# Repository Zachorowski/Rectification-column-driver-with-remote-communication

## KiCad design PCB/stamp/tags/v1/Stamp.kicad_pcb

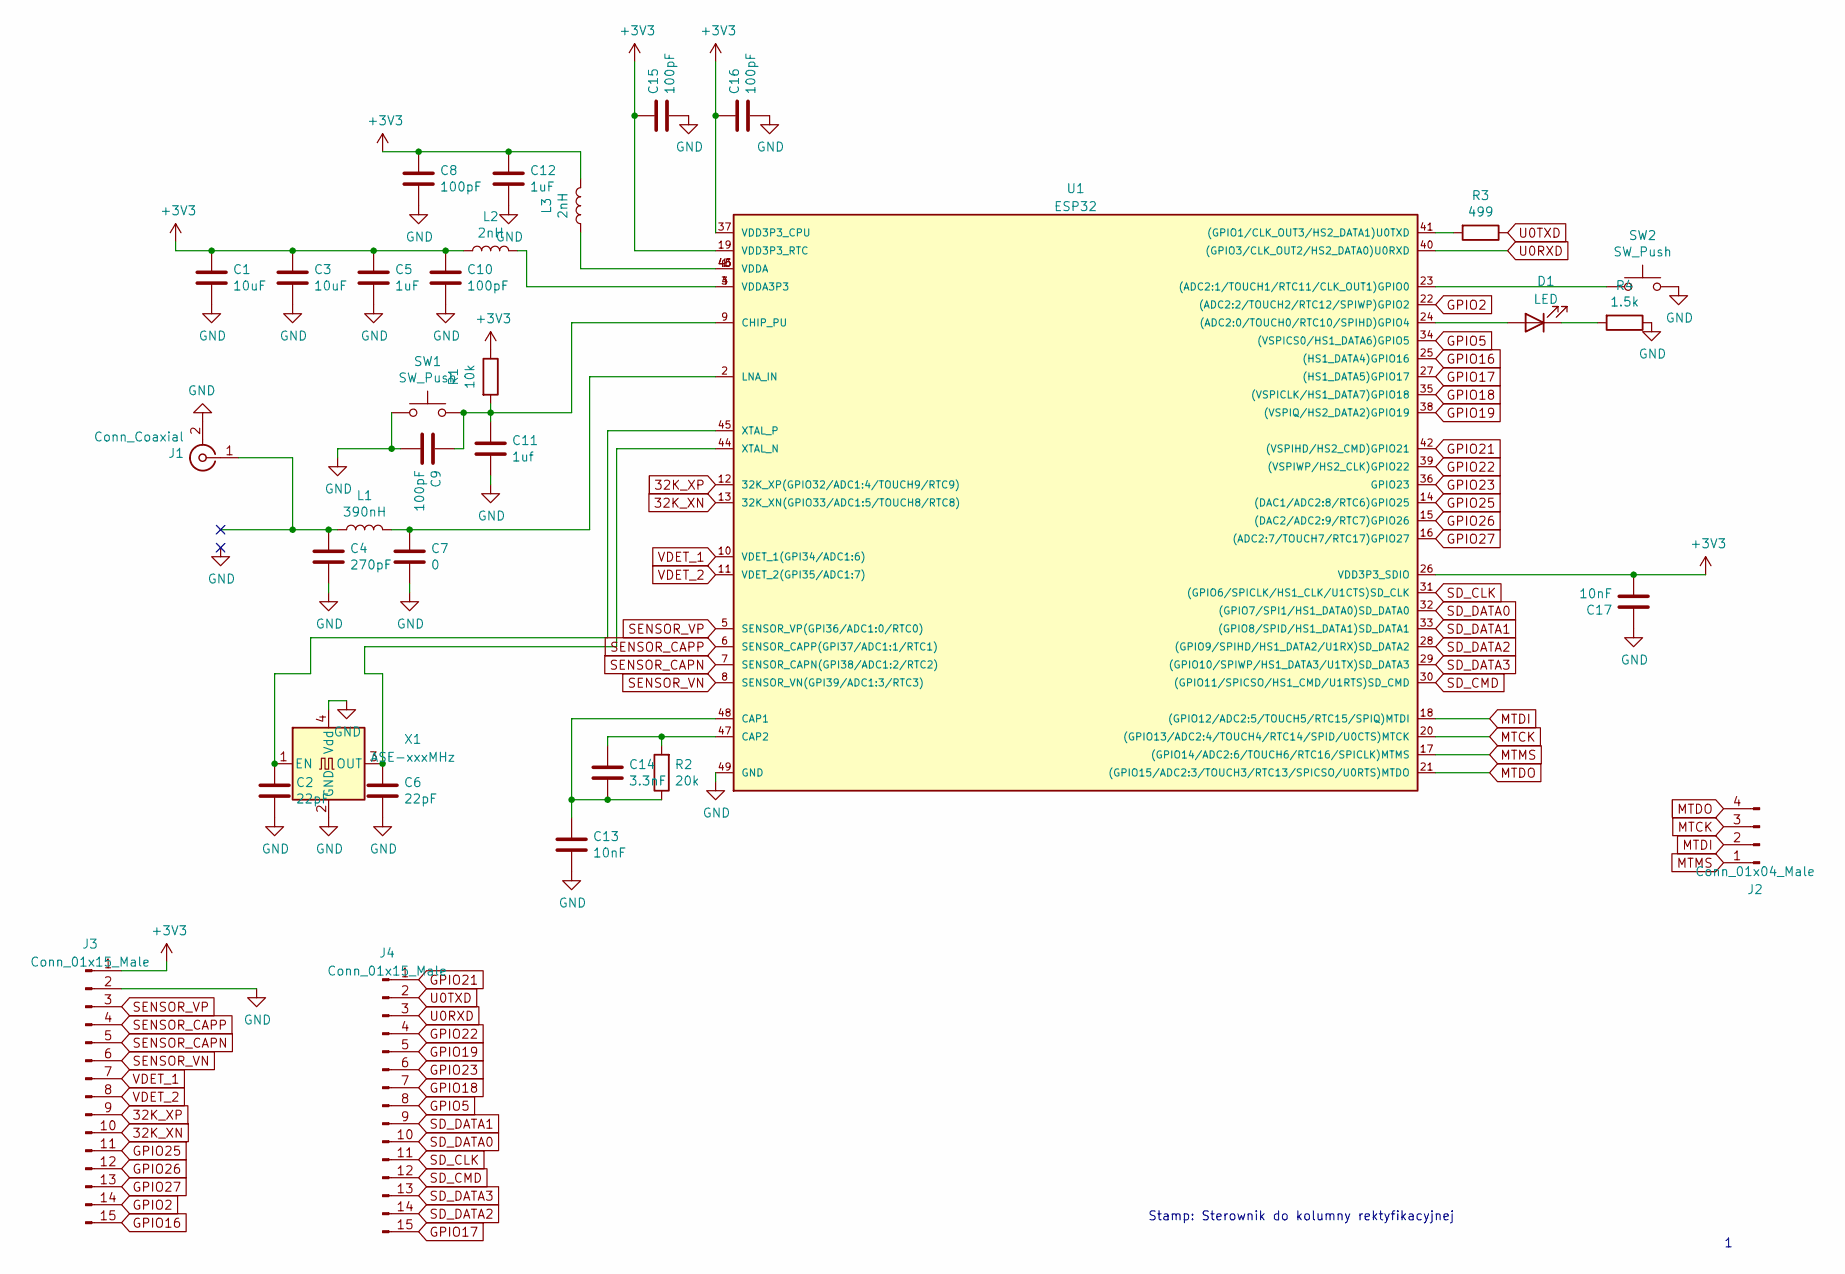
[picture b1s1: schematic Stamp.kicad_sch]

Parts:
C1, C3: 10uF; C_0603_1608Metric_Pad1.08x0.95mm_HandSolder
C2, C6: 22pF; C_0603_1608Metric_Pad1.08x0.95mm_HandSolder
C4: 270pF; C_0603_1608Metric_Pad1.08x0.95mm_HandSolder
C5, C12: 1uF; C_0603_1608Metric_Pad1.08x0.95mm_HandSolder
C7: 0; C_0603_1608Metric_Pad1.08x0.95mm_HandSolder
C8, C9, C10, C15, C16: 100pF; C_0603_1608Metric_Pad1.08x0.95mm_HandSolder
C11: 1uf; C_0603_1608Metric_Pad1.08x0.95mm_HandSolder
C13, C17: 10nF; C_0603_1608Metric_Pad1.08x0.95mm_HandSolder
C14: 3.3nF; C_0603_1608Metric_Pad1.08x0.95mm_HandSolder
D1: LED; LED_0805_2012Metric_Pad1.15x1.40mm_HandSolder
J1: Conn_Coaxial; U.FL_Molex_MCRF_73412-0110_Vertical
J2: Conn_01x04_Male; PinHeader_1x04_P2.54mm_Vertical
J3, J4: Conn_01x15_Male; PinHeader_1x15_P2.54mm_Vertical
L1: 390nH; L_0603_1608Metric_Pad1.05x0.95mm_HandSolder
L2, L3: 2nH; L_0603_1608Metric_Pad1.05x0.95mm_HandSolder
R1: 10k; R_0603_1608Metric_Pad0.98x0.95mm_HandSolder
R2: 20k; R_0603_1608Metric_Pad0.98x0.95mm_HandSolder
R3: 499; R_0603_1608Metric_Pad0.98x0.95mm_HandSolder
R4: 1.5k; R_0603_1608Metric_Pad0.98x0.95mm_HandSolder
SW1, SW2: SW_Push; SW_Push_1P1T_NO_6x6mm_H9.5mm
U1: ESP32; QFN-48-1EP_6x6mm_P0.4mm_EP4.3x4.3mm
X1: ASE-xxxMHz; Oscillator_SMD_SeikoEpson_SG210-4Pin_2.5x2.0mm_HandSoldering

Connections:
32K_XN: J3.10, U1.13 (32K_XN(GPIO33/ADC1:5/TOUCH8/RTC8))
32K_XP: J3.9, U1.12 (32K_XP(GPIO32/ADC1:4/TOUCH9/RTC9))
+3V3: C1.2, C3.2, C5.2, C8.2, C10.2, C12.2, C15.2, C16.2, C17.1, J3.1, L2.1, L3.2, R1.1, U1.19 (VDD3P3_RTC), U1.26 (VDD3P3_SDIO), U1.37 (VDD3P3_CPU)
GND: C1.1, C2.1, C3.1, C4.1, C5.1, C6.1, C7.1, C8.1, C9.1, C10.1, C11.1, C12.1, C13.1, C15.1, C16.1, C17.2, J1.2 (Ext), J3.2, R4.1, SW1.1, SW2.2, U1.49 (GND), X1.2 (GND), X1.4 (Vdd)
GPIO2: J3.14, U1.22 ((ADC2:2/TOUCH2/RTC12/SPIWP)GPIO2)
GPIO5: J4.8, U1.34 ((VSPICS0/HS1_DATA6)GPIO5)
GPIO16: J3.15, U1.25 ((HS1_DATA4)GPIO16)
GPIO17: J4.15, U1.27 ((HS1_DATA5)GPIO17)
GPIO18: J4.7, U1.35 ((VSPICLK/HS1_DATA7)GPIO18)
GPIO19: J4.5, U1.38 ((VSPIQ/HS2_DATA2)GPIO19)
GPIO21: J4.1, U1.42 ((VSPIHD/HS2_CMD)GPIO21)
GPIO22: J4.4, U1.39 ((VSPIWP/HS2_CLK)GPIO22)
GPIO23: J4.6, U1.36 (GPIO23)
GPIO25: J3.11, U1.14 ((DAC1/ADC2:8/RTC6)GPIO25)
GPIO26: J3.12, U1.15 ((DAC2/ADC2:9/RTC7)GPIO26)
GPIO27: J3.13, U1.16 ((ADC2:7/TOUCH7/RTC17)GPIO27)
MTCK: J2.3, U1.20 ((GPIO13/ADC2:4/TOUCH4/RTC14/SPID/U0CTS)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)
MTDI: J2.2, U1.18 ((GPIO12/ADC2:5/TOUCH5/RTC15/SPIQ)MTDI)
MTDO: J2.4, U1.21 ((GPIO15/ADC2:3/TOUCH3/RTC13/SPICSO/U0RT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)
MTMS: J2.1, U1.17 ((GPIO14/ADC2:6/TOUCH6/RTC16/SPICLK)MTMS)
unnamed: C2.2, U1.45 (XTAL_P), X1.1 (EN)
unnamed: C6.2, U1.44 (XTAL_N), X1.3 (OUT)
unnamed: C7.2, L1.2, U1.2 (LNA_IN)
unnamed: C9.2, C11.2, R1.2, SW1.2, U1.9 (CHIP_PU)
unnamed: C13.2, C14.1, R2.1, U1.48 (CAP1)
unnamed: C14.2, R2.2, U1.47 (CAP2)
unnamed: D1.1 (K), R4.2
unnamed: D1.2 (A), U1.24 ((ADC2:0/TOUCH0/RTC10/SPIHD)GPIO4)
unnamed: L2.2, U1.3 (VDDA3P3), U1.4 (VDDA3P3)
unnamed: L3.1, U1.1 (VDDA), U1.43 (VDDA), U1.46 (VDDA)
unnamed: R3.2, U1.41 ((GPIO1/CLK_OUT3/HS2_DATA1)U0TXD)
unnamed: SW2.1, U1.23 ((ADC2:1/TOUCH1/RTC11/CLK_OUT1)GPIO0)
SD_CLK: J4.11, U1.31 ((GPIO6/SPICLK/HS1_CLK/U1CTS)SD_CLK)
SD_CMD: J4.12, U1.30 ((GPIO11/SPICSO/HS1_CMD/U1RTS)SD_CMD)
SD_DATA0: J4.10, U1.32 ((GPIO7/SPI1/HS1_DATA0)SD_DATA0)
SD_DATA1: J4.9, U1.33 ((GPIO8/SPID/HS1_DATA1)SD_DATA1)
SD_DATA2: J4.14, U1.28 ((GPIO9/SPIHD/HS1_DATA2/U1RX)SD_DATA2)
SD_DATA3: J4.13, U1.29 ((GPIO10/SPIWP/HS1_DATA3/U1TX)SD_DATA3)
SENSOR_CAPN: J3.5, U1.7 (SENSOR_CAPN(GPI38/ADC1:2/RTC2))
SENSOR_CAPP: J3.4, U1.6 (SENSOR_CAPP(GPI37/ADC1:1/RTC1))
SENSOR_VN: J3.6, U1.8 (SENSOR_VN(GPI39/ADC1:3/RTC3))
SENSOR_VP: J3.3, U1.5 (SENSOR_VP(GPI36/ADC1:0/RTC0))
U0RXD: J4.3, U1.40 ((GPIO3/CLK_OUT2/HS2_DATA0)U0RXD)
U0TXD: J4.2, R3.1
VDET_1: J3.7, U1.10 (VDET_1(GPI34/ADC1:6))
VDET_2: J3.8, U1.11 (VDET_2(GPI35/ADC1:7))

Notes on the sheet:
Stamp: Sterownik do kolumny rektyfikacyjnej

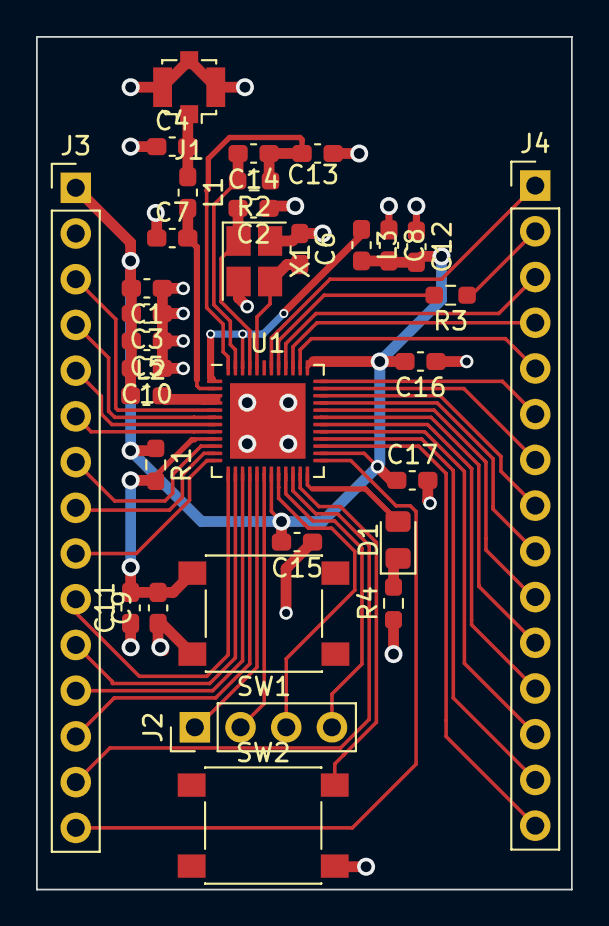
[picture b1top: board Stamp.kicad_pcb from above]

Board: 2 copper layers, 29.7 x 47.4 mm, 33 parts (0 on the bottom side), 46 nets.

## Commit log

2022-06-24 destiler-V1
